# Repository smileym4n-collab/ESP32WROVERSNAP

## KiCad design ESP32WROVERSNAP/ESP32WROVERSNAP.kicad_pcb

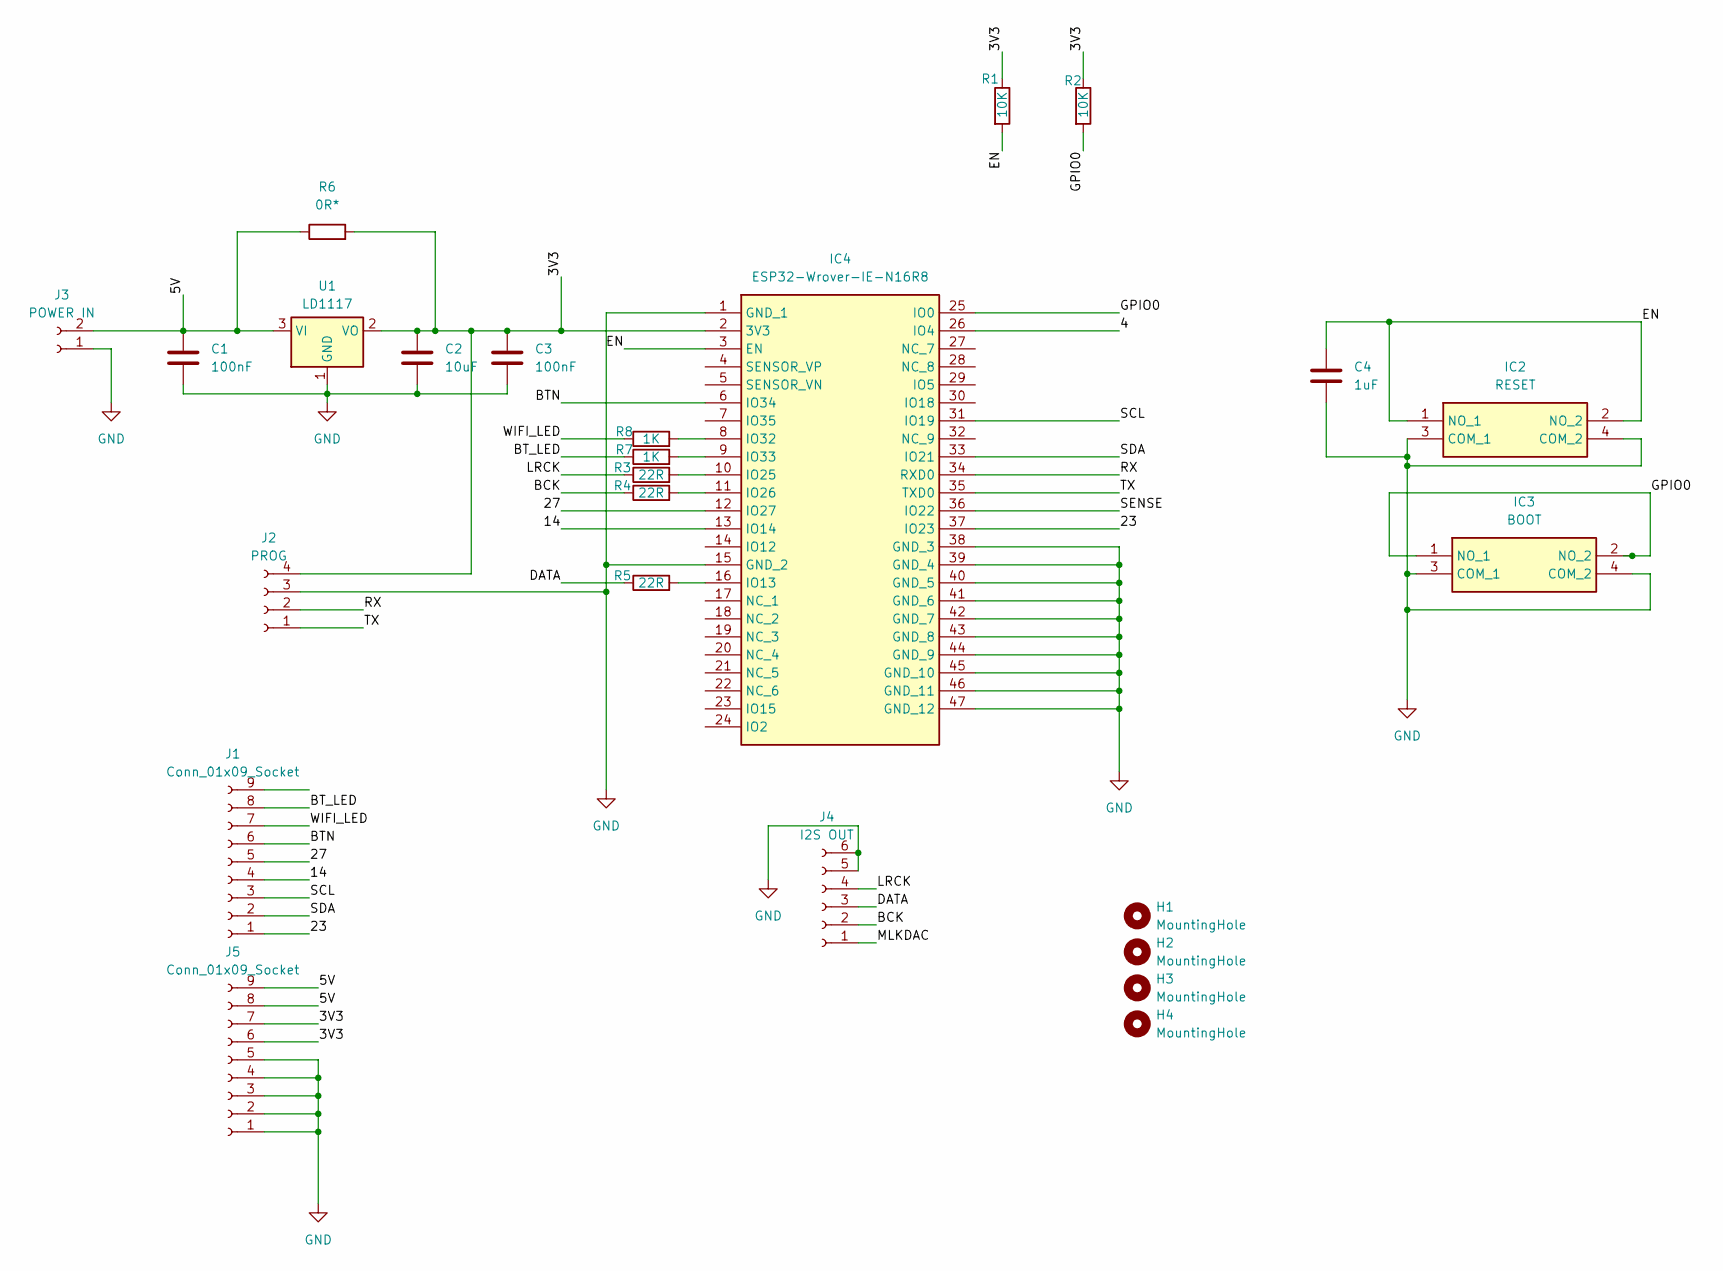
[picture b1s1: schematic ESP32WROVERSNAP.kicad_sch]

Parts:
C1, C3: 100nF; C_1206_3216Metric_Pad1.33x1.80mm_HandSolder
C2: 10uF; C_0805_2012Metric_Pad1.18x1.45mm_HandSolder
C4: 1uF; C_1206_3216Metric_Pad1.33x1.80mm_HandSolder
H1, H2, H3, H4: MountingHole; MountingHole_4mm
IC2: RESET; TS026650BK100SCRD; Mouser Part Number 179-TS026650BK100SCR
IC3: BOOT; TS026650BK100SCRD; Mouser Part Number 179-TS026650BK100SCR
IC4: ESP32-Wrover-IE-N16R8; ESP32-WROVER-IE-N16R8; Mouser Part Number 356-ESP32WRVIE2864UC
J1, J5: Conn_01x09_Socket; PinHeader_1x09_P2.54mm_Vertical
J2: PROG; PinHeader_1x04_P2.54mm_Vertical
J3: POWER IN; JST_XH_B2B-XH-A_1x02_P2.50mm_Vertical
J4: I2S OUT; JST_XH_B6B-XH-A_1x06_P2.50mm_Vertical
R1, R2: 10K; R_0603_1608Metric_Pad0.98x0.95mm_HandSolder
R3, R4, R5: 22R; R_0603_1608Metric_Pad0.98x0.95mm_HandSolder
R6: 0R*; R_0805_2012Metric_Pad1.20x1.40mm_HandSolder
R7, R8: 1K; R_0805_2012Metric_Pad1.20x1.40mm_HandSolder
U1: LD1117; SOT-223-3_TabPin2

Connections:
/3V3: C2.1, C3.1, IC4.2 (3V3), J2.4, J5.6, J5.7, R1.1, R2.1, R6.2, U1.2 (VO)
/4: IC4.26 (IO4)
/5V: C1.1, J3.2, J5.8, J5.9, R6.1, U1.3 (VI)
/14: IC4.13 (IO14), J1.4
/23: IC4.37 (IO23), J1.1
/27: IC4.12 (IO27), J1.5
/BCK: J4.2, R4.1
/BTN: IC4.6 (IO34), J1.6
/BT_LED: J1.8, R7.1
/DATA: J4.3, R5.1
/EN: C4.1, IC2.1 (NO_1), IC2.2 (NO_2), IC4.3 (EN), R1.2
/GPIO0: IC3.1 (NO_1), IC3.2 (NO_2), IC4.25 (IO0), R2.2
/LRCK: J4.4, R3.1
/MLKDAC: J4.1
/RX: IC4.34 (RXD0), J2.2
/SCL: IC4.31 (IO19), J1.3
/SDA: IC4.33 (IO21), J1.2
/SENSE: IC4.36 (IO22)
/TX: IC4.35 (TXD0), J2.1
/WIFI_LED: J1.7, R8.1
GND: C1.2, C2.2, C3.2, C4.2, IC2.3 (COM_1), IC2.4 (COM_2), IC3.3 (COM_1), IC3.4 (COM_2), IC4.1 (GND_1), IC4.15 (GND_2), IC4.38 (GND_3), IC4.39 (GND_4), IC4.40 (GND_5), IC4.41 (GND_6), IC4.42 (GND_7), IC4.43 (GND_8), IC4.44 (GND_9), IC4.45 (GND_10), IC4.46 (GND_11), IC4.47 (GND_12), J2.3, J3.1, J4.5, J4.6, J5.1, J5.2, J5.3, J5.4, J5.5, U1.1 (GND)
unnamed: IC4.16 (IO13), R5.2
unnamed: IC4.10 (IO25), R3.2
unnamed: IC4.11 (IO26), R4.2
unnamed: IC4.8 (IO32), R8.2
unnamed: IC4.9 (IO33), R7.2

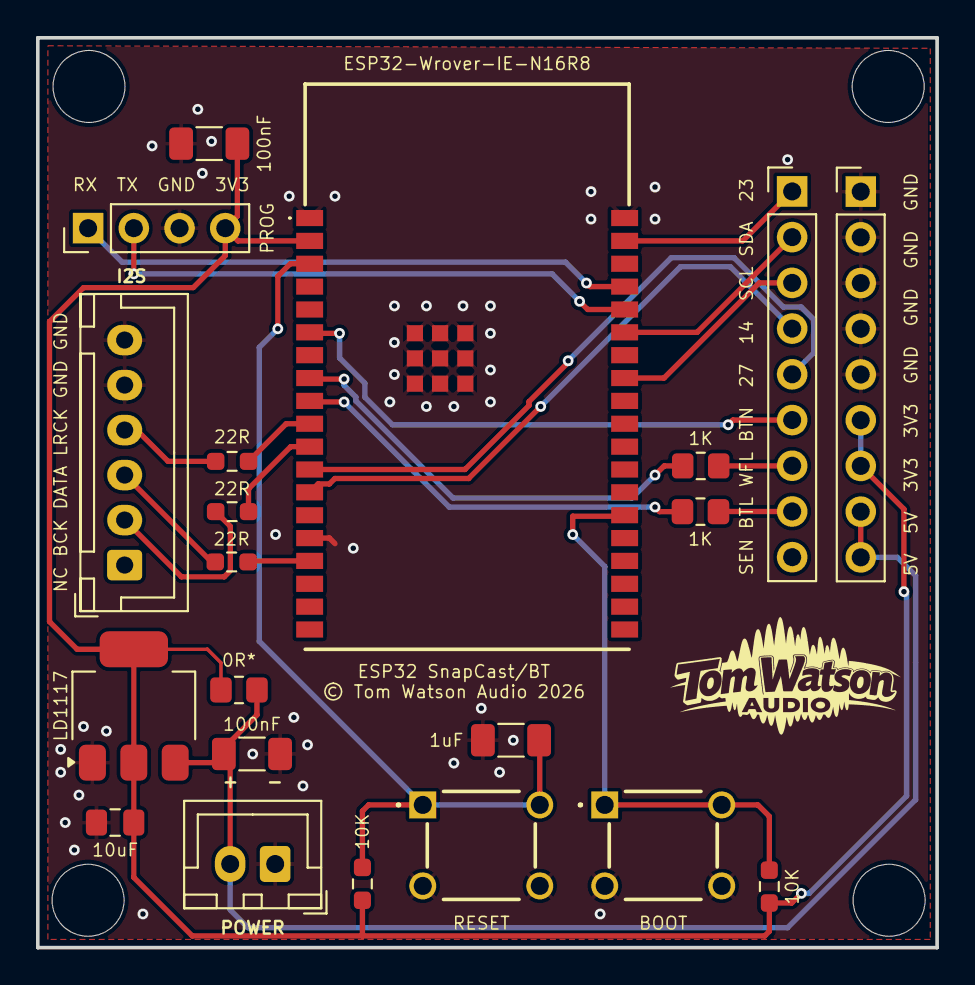
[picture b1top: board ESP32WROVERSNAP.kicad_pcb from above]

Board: 2 copper layers, 50.0 x 50.5 mm, 25 parts (0 on the bottom side), 23 nets.

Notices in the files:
ESP32WROVERSNAP/ESP32WROVERSNAP.kicad_pcb:
© Tom Watson Audio 2026
